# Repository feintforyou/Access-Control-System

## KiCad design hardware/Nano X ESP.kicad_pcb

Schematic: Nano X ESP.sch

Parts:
AE1: Antenna_Shield; U.FL_Molex_MCRF_73412-0110_Vertical
C1: 100nF; C_0805_2012Metric_Pad1.18x1.45mm_HandSolder
C2, C3: 22pF; C_0805_2012Metric_Pad1.18x1.45mm_HandSolder
C4, C6, C7, C8, C10: 10uF; C_0805_2012Metric_Pad1.18x1.45mm_HandSolder
C5, C9, C11: 10nF; C_0805_2012Metric_Pad1.18x1.45mm_HandSolder
H1, H2, H3, H4: MountingHole; MountingHole_3.5mm
J1, J3: Conn_ESP; PinHeader_1x06_P2.54mm_Vertical
J2, J4: Conn_Atmega; PinHeader_1x11_P2.54mm_Vertical
J5: Conn_FT232; PinHeader_1x06_P2.54mm_Vertical
J6: CONN_SIM800l; PinHeader_1x02_P2.54mm_Vertical
J7: CONN_Input; PinHeader_1x02_P2.54mm_Vertical
J8: Conn_SPI; PinHeader_1x06_P2.54mm_Vertical
J9: Conn_I2C; PinHeader_1x04_P2.54mm_Vertical
J10: Conn_Output; PinHeader_1x03_P2.54mm_Vertical
JP1: SolderJumper_Arduino+; SolderJumper-2_P1.3mm_Open_RoundedPad1.0x1.5mm
JP2: SolderJumper_ESP+; SolderJumper-2_P1.3mm_Open_RoundedPad1.0x1.5mm
JP3: Bypass_GND_Sim800l; SolderJumper-2_P1.3mm_Open_RoundedPad1.0x1.5mm
JP4: Bypass_Sim800l; SolderJumper-2_P1.3mm_Open_RoundedPad1.0x1.5mm
JP5: Bypass_AtMega; SolderJumper-2_P1.3mm_Open_RoundedPad1.0x1.5mm
JP6: Bypass_VoltReg; SolderJumper-2_P1.3mm_Open_RoundedPad1.0x1.5mm
Q1, Q2: S8050; SOT-23
R1: 1K; R_0805_2012Metric_Pad1.20x1.40mm_HandSolder
R2, R3, R4, R5, R8, R9, R10, R11, R12: 10K; R_0805_2012Metric_Pad1.20x1.40mm_HandSolder
SW1: SW_Reset; SW_SPST_FSMSM
SW2: SW_RESET; SW_SPST_FSMSM
U1: AMS1117-3.3; SOT-223-3_TabPin2
U2: ATmega328-AU; TQFP-32_7x7mm_P0.8mm
U3: ESP-07
U4: RFM95W-868S2; HOPERF_RFM9XW_SMD
U5: SIM800; sim800l
Y1: 16.000 Mhz; Crystal_SMD_HC49-SD

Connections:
+3V3: C6.1, J10.2, JP2.1 (A), JP4.1 (A), JP5.1 (A), JP6.1 (A), U1.2 (VO), U4.13 (3.3V)
+4V: J6.1, JP4.2 (B), U5.2
+5V: C4.1, J5.6, J7.1, J10.1, JP1.1 (A), JP6.2 (B), U1.3 (VI)
/A0: J2.1, U2.23 (PC0)
/A1: J2.2, U2.24 (PC1)
/A2: J2.3, U2.25 (PC2)
/A3: J2.4, U2.26 (PC3)
/A4: J2.5, J3.4, J9.4, U2.27 (PC4), U3.13 (GPIO4)
/A5: J2.6, J3.3, J9.3, U2.28 (PC5), U3.14 (GPIO5)
/A6: J2.7, U2.19 (ADC6)
/A7: J2.8, U2.22 (ADC7)
/ADC: R10.1, R12.2, U3.2 (ADC)
/ADCIN: J1.1, R12.1
/CS: J1.6, J4.4, J8.6, R11.1, U2.14 (PB2), U3.10 (GPIO15), U4.5 (NSS)
/D0: J2.9, J3.1, J5.1, U2.30 (PD0), U3.15 (GPIO3/RXD), U5.5
/D1: J2.10, J3.2, J5.2, U2.31 (PD1), U3.16 (GPIO1/TXD), U5.4
/D2: J2.11, J3.6, R5.1, U2.32 (PD2), U3.11 (GPIO2), U4.14 (DIO0)
/D3: J4.11, U2.1 (PD3)
/D4: J4.10, U2.2 (PD4)
/D5: J4.9, U2.9 (PD5)
/D6: J4.8, U2.10 (PD6)
/D7: J4.7, U2.11 (PD7)
/D8: J4.6, U2.12 (PB0)
/D9: J4.5, U2.13 (PB1)
/D11: J1.5, J4.3, J8.5, U2.15 (PB3), U3.7 (GPIO13), U4.3 (MOSI)
/D12: J1.4, J4.2, J8.4, U2.16 (PB4), U3.6 (GPIO12), U4.2 (MISO)
/D13: J1.3, J4.1, J8.3, U2.17 (PB5), U3.5 (GPIO14), U4.4 (SCK)
/DTR: C1.1, J5.3, Q2.1 (E), R8.2
/EN: R3.1, U3.3 (EN)
/GPIO0: J3.5, Q1.1 (E), R4.1, U3.12 (GPIO0)
/GPIO16: J1.2, U3.4 (GPIO16)
/RESET: C1.2, R1.2, SW1.1, U2.29 (~RESET~/PC6)
/RST: C9.2, Q2.3 (C), R2.1, SW2.2, U3.1 (~RST)
/RST_GSM: U5.3
/RTS: J5.4, Q1.3 (C), R9.2
/XTAL1: C3.1, U2.7 (XTAL1/PB6), Y1.2
/XTAL2: C2.2, U2.8 (XTAL2/PB7), Y1.1
GND: AE1.2, C2.1, C3.2, C4.2, C5.2, C6.2, C7.2, C8.2, C9.1, C10.2, C11.1, J5.5, J7.2, J8.2, J9.2, J10.3, JP3.1 (A), R10.2, R11.2, SW1.2, SW2.1, U1.1 (GND), U2.3 (GND), U2.5 (GND), U2.21 (GND), U3.9 (GND), U4.1 (GND), U4.8 (GND), U4.10 (GND)
GND1: J6.2, JP3.2 (B), U5.6
unnamed: AE1.1, U4.9 (ANT)
unnamed: C5.1, U2.20 (AREF)
unnamed: Q1.2 (B), R8.1
unnamed: Q2.2 (B), R9.1
VCC: C7.1, C8.1, J8.1, J9.1, JP1.2 (B), JP5.2 (B), R1.1, U2.4 (VCC), U2.6 (VCC), U2.18 (AVCC)
VDD: C10.1, C11.2, JP2.2 (B), R2.2, R3.2, R4.2, R5.2, U3.8 (VCC)

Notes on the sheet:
Arduino Nano
ESP 8266
SIM800 Management
Power Supply
LORA Management
Connector

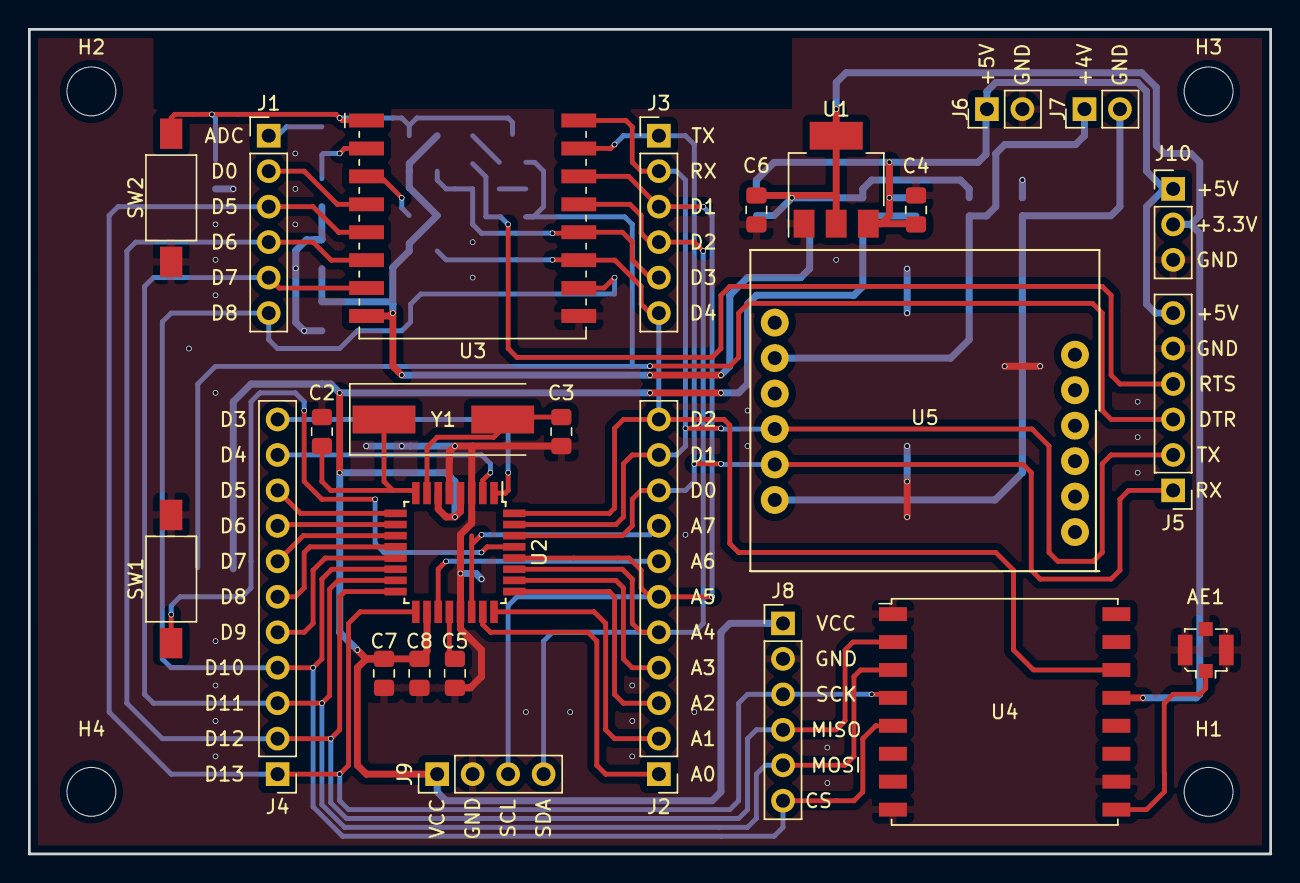
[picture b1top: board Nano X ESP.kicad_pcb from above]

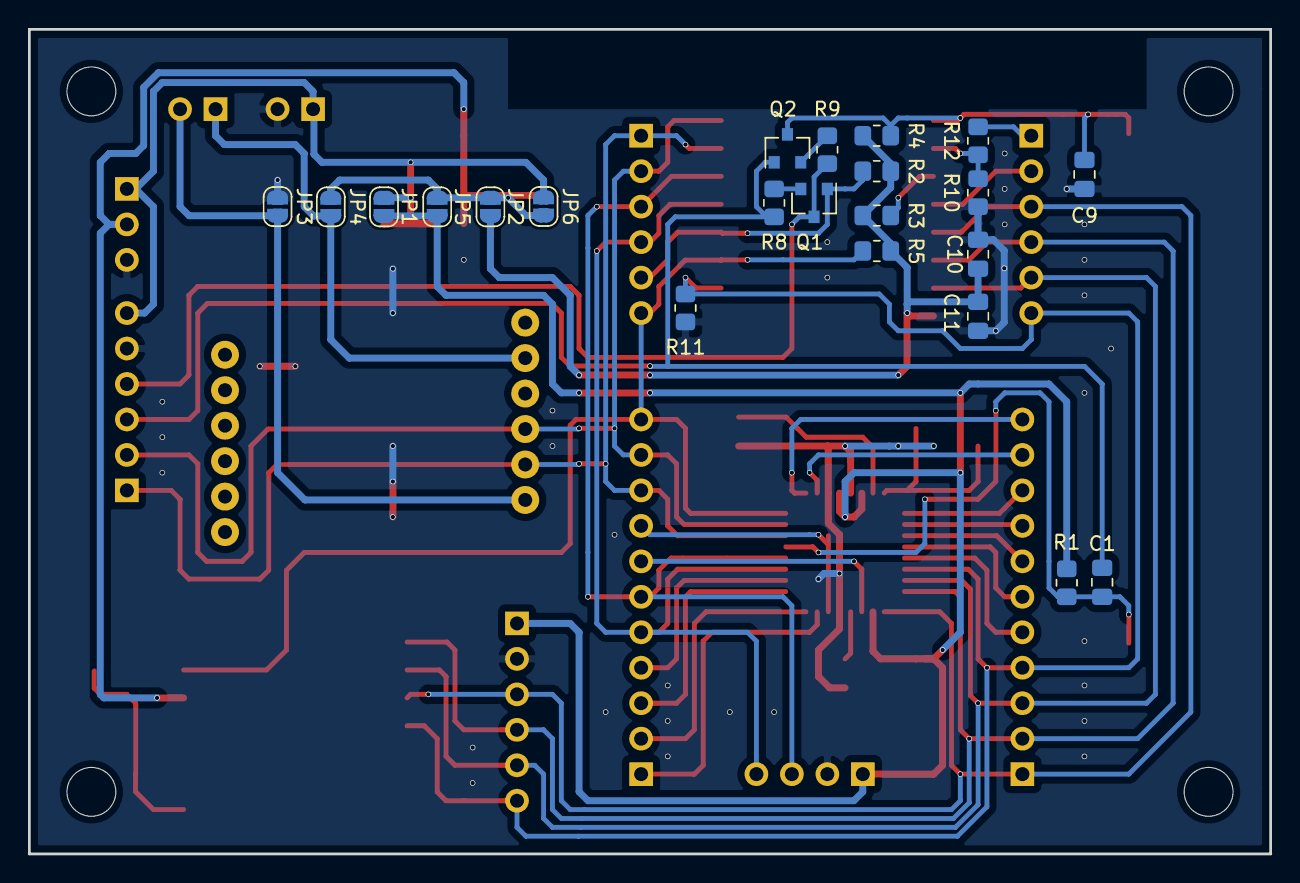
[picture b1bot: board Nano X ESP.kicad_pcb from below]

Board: 2 copper layers, 88.9 x 59.1 mm, 52 parts (22 on the bottom side), 44 nets.

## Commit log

2021-08-26 try to commit
2021-08-27 add kicad file
2021-09-13 fixed version 1
